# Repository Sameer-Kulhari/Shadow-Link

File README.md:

# Shadow-Link
A diy high performance Transmitter Module with ELRS support and custom hardware which can transmit data using Sx1280 RF module and ESP-32.
This Transmitter module works on a open source Firmware called ELRS ,which is used in high end transmitters and recievers

# Features :
- 15km + range (LOS)
- 5ms latency
- Oled and RGB
- External Antenna
- ELRS support
- Custom case and Pcb
- Works on Uart
- Works with any ELRS reciever

# Purpose :
- I made this transmitter module for my future projects in which they need a device to transfer data wirelessly , for long range and quickly ,So i made this transmitter module,So I can just send data to this module via Uart and receive on other side using any ELRS reciever.

# Parts Used :
- ESP-32 WROOM
- E28-2G4M27S (SX1280)
- NEOPIXEL (WS2812)
- 0.96" I2C SSD1306
- MP1584 Step Down Regulator

# Images :
**PCB :**

**CAD :**

# BOM :
| Supplier             | Item                                           | Price (USD) |
|----------------------|------------------------------------------------|-------------|
| **Quartz Components**| Oled SSD1306                                   | $1.60       |
|                      | MP1584 Voltage Regulator                       | $0.50       |
|                      | RG81 Ipex to SMA                               | $0.50       |
|                      | 12 dbi Antenna                                 | $2.10       |
|                      | Usb to TTl converter                           | $0.70       |
|                      | Colling Fan                                    | $0.84       |
|                      | Battery                                        | $3.26       |
|                      | Misc                                           | $2.00       |
|                      | Shipping                                       | $2.54       |
|                      | **Total (Quartz Components)**                  | **$13.94**  |
| **Lion Circuits**    | PCB                                            | $11.54      |
|                      | Shipping                                       | $2.33       |
|                      | **Total (Lion Circuits)**                      | **$13.87**  |
| **SemiNest**         | E28-2G4M27S                                    | $16.9       |
|                      | ESP32-WROOM-32E-N16                            | $8.85       |
|                      | Shipping                                       | $2.33       |
|                      | **Total (SemiNest)**                           | **$28.08**  |
|----------------------|------------------------------------------------|-------------|
|**Total**             |                                                | **$55.89**  |

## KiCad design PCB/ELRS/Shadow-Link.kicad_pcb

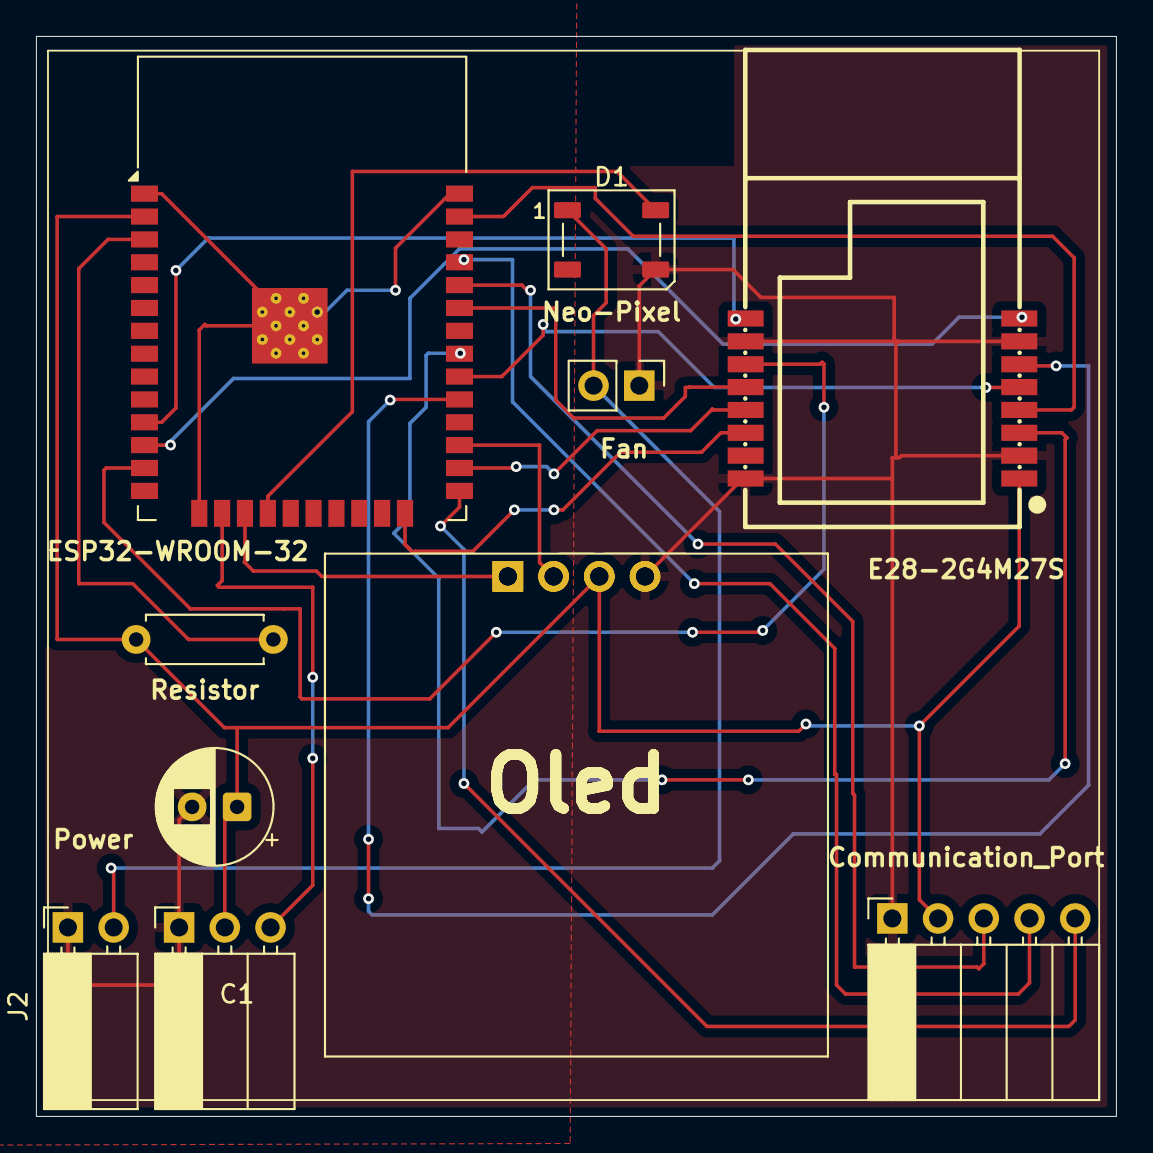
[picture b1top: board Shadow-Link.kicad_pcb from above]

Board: 2 copper layers, 60.0 x 60.0 mm, 11 parts (0 on the bottom side), 22 nets.

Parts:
C1: C_Polarized; CP_Radial_D6.3mm_P2.50mm
Communication_Port: Conn_01x05_Socket; PinSocket_1x05_P2.54mm_Horizontal
D1: Neo-Pixel; LED_WS2812B_PLCC4_5.0x5.0mm_P3.2mm
J1, J1#2: Oled; OLED_128x64
J2: Power; PinSocket_1x02_P2.54mm_Horizontal
J3: Fan; PinHeader_1x02_P2.54mm_Vertical
Power: Conn_01x03_Socket; PinSocket_1x03_P2.54mm_Horizontal
R1: Resistor; R_Axial_DIN0207_L6.3mm_D2.5mm_P7.62mm_Horizontal
U1: ESP32-WROOM-32
U2: WIRELM-SMD_E28-2G4M2XS

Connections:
+3V3: C1.1, Communication_Port.2, J1.3, J1#2.3, Power.2, R1.1, U1.2 (VDD), U2.1 (VCC)
+5V: D1.1 (VDD), J2.2, J3.2
/BOOT0: Communication_Port.5, U1.25 (IO0)
/BUSY: U1.33 (IO21), U2.12 (BUSY)
/DI01: U1.26 (IO4), U2.13 (DIO1)
/DI02: U1.24 (IO2), U2.14 (DIO2)
/DIN: D1.4 (DIN), U1.18 (SWP/SD3)
/MISO: U1.31 (IO19), U2.3 (MISO_TX)
/MOSI: U1.37 (IO23), U2.4 (MOSI_RX)
/NRESET: U1.13 (IO14), U2.11 (NRESET)
/NSS: U1.29 (IO5), U2.6 (NSS_CTS)
/RX: Communication_Port.3, U1.34 (RXD0/IO3)
/RX_EN: U1.12 (IO27), U2.8 (RX_EN)
/SCK: U1.30 (IO18), U2.5 (SCK_RTSN)
/SCL: J1.2, J1#2.2, U1.27 (IO16)
/SDA: J1.1, J1#2.1, U1.17 (SHD/SD2)
/SPORT: Power.3, U1.16 (IO13)
/TX: Communication_Port.4, U1.35 (TXD0/IO1)
/TX_EN: U1.11 (IO26), U2.9 (TX_EN)
GND: C1.2, Communication_Port.1, D1.3 (VSS), J1.4, J1#2.4, J2.1, J3.1, Power.1, U2.2 (GND), U2.7 (GND), U2.10 (GND), U2.16 (GND)
unnamed: R1.2, U1.3 (EN)
unnamed: U1.1 (GND), U1.15 (GND), U1.38 (GND), U1.39 (GND)

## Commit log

2025-07-09 June-8th
2025-07-09 June 8th
2025-07-09 June 9th
2025-07-09 Updated file structure
2025-07-12 New Version
2025-07-12 Updated version
2025-07-13 3d Model Added
2025-07-13 Create Firmware
2025-07-13 Uploaded Firmware
2025-07-13 Uploaded Schematic
2025-07-13 Added BOM
